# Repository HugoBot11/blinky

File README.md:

# Blinky
555 LED chaser board
I made this project to learn about making PCBs.
Made through Hack Club workshop Blueprint.

|Designator|Footprint|Quantity|Value|
|---|---|---|---|
|C1|CP_Radial_D5.0mm_P2.00mm|1|1 uF|
|C2|CP_Radial_D5.0mm_P2.00mm|1|0.01uF|
|D1, D2, D3, D4, D5, D6, D7, D8, D9, D10|LED_D3.0mm|10|LED|
|R1|R_Axial_DIN0207_L6.3mm_D2.5mm_P7.62mm_Horizontal|1|1k|
|R2|R_Axial_DIN0207_L6.3mm_D2.5mm_P7.62mm_Horizontal|1|470|
|RV1|R_Axial_DIN0207_L6.3mm_D2.5mm_P7.62mm_Horizontal|1|50k|
|U1|DIP-8_W7.62mm|1|NE555P|
|U2|N16|1|4017|

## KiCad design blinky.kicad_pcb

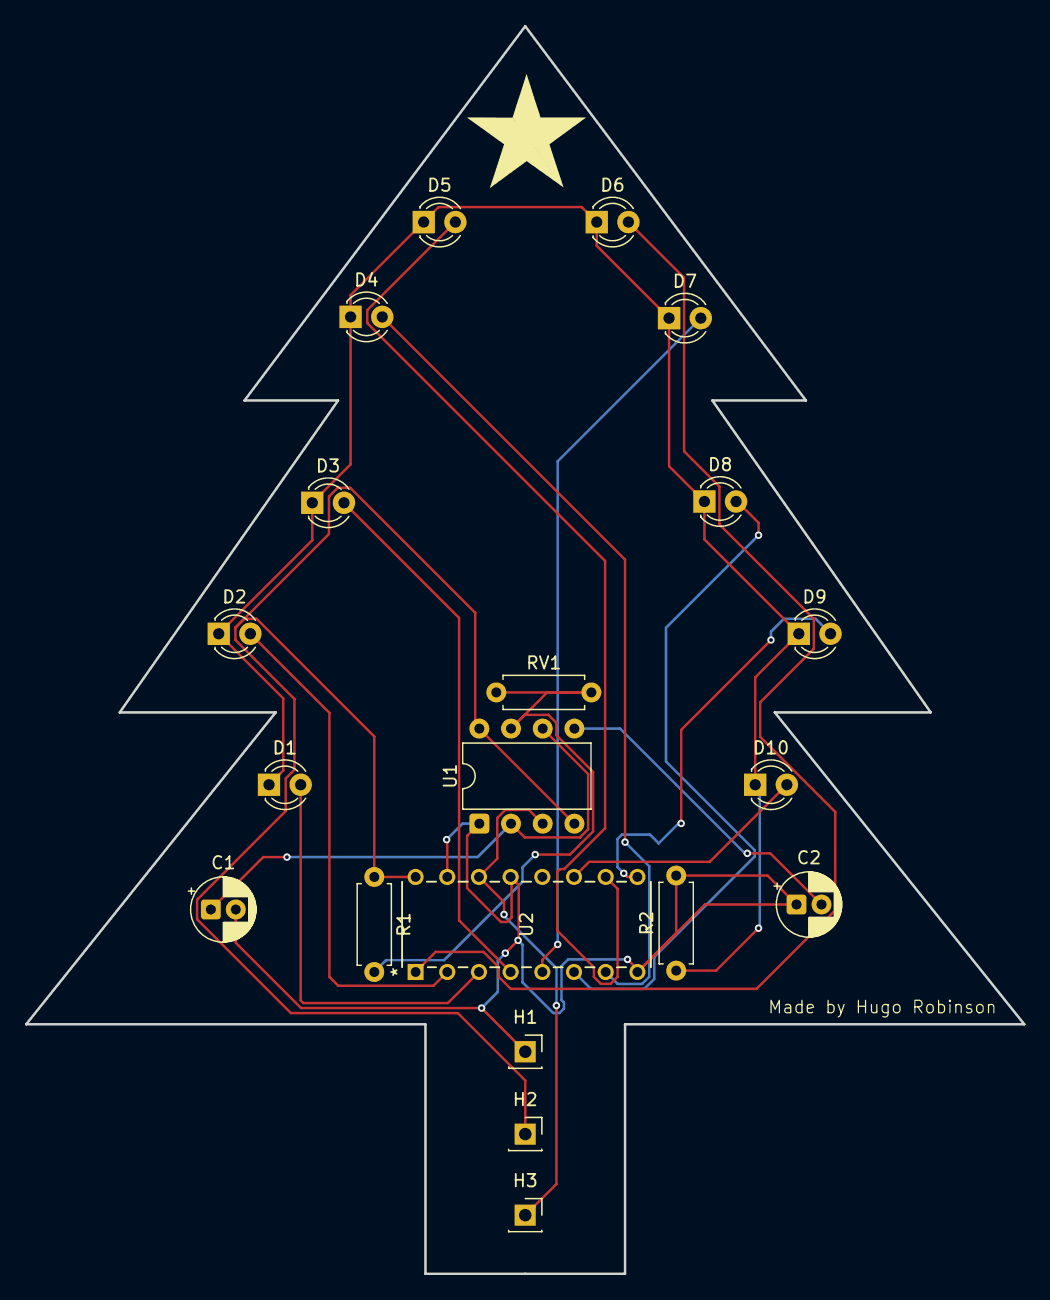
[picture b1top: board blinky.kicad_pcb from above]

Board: 2 copper layers, 80.0 x 100.0 mm, 20 parts (0 on the bottom side), 17 nets.

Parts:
C1: 1 uF; CP_Radial_D5.0mm_P2.00mm
C2: 0.01 uF; CP_Radial_D5.0mm_P2.00mm
D1, D2, D3, D4, D5, D6, D7, D8, D9, D10: LED; LED_D3.0mm
H1, H2, H3: MountingHole_Pad; PinSocket_1x01_P2.54mm_Vertical
R1: 1k; R_Axial_DIN0207_L6.3mm_D2.5mm_P7.62mm_Horizontal
R2: 470; R_Axial_DIN0207_L6.3mm_D2.5mm_P7.62mm_Horizontal
RV1: 50k; R_Axial_DIN0207_L6.3mm_D2.5mm_P7.62mm_Horizontal
U1: NE555P; DIP-8_W7.62mm
U2: 4017; N16

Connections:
+5V: H2.1, R1.1, U1.4 (R), U1.8 (VCC), U2.16 (VDD)
GND: C1.2, C2.1, H1.1, R2.2, U1.1 (GND), U2.8 (VSS), U2.13 (CKEN), U2.15 (Reset)
unnamed: D1.2 (A), U2.3 (Q0)
unnamed: D1.1 (K), D2.1 (K), D3.1 (K), D4.1 (K), D5.1 (K), D6.1 (K), D7.1 (K), D8.1 (K), D9.1 (K), D10.1 (K), R2.1
unnamed: D2.2 (A), U2.2 (Q1)
unnamed: D3.2 (A), U2.4 (Q2)
unnamed: D4.2 (A), U2.7 (Q3)
unnamed: D5.2 (A), U2.10 (Q4)
unnamed: D6.2 (A), U2.1 (Q5)
unnamed: D7.2 (A), U2.5 (Q6)
unnamed: D8.2 (A), U2.6 (Q7)
unnamed: D9.2 (A), U2.9 (Q8)
unnamed: D10.2 (A), U2.11 (Q9)
unnamed: C2.2, U1.5 (CV)
unnamed: R1.2, RV1.1, RV1.2, U1.7 (DIS)
OUT: H3.1, U1.3 (Q), U2.14 (CLK)
TR: C1.1, U1.2 (TR), U1.6 (THR)

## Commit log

2026-03-29 Update README with project name and details
    Corrected the capitalization of the project name and added a description along with an image.
2026-03-29 Enhance README with project details and components
    Expanded project description and added component table.
